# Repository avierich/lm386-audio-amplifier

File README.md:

# lM386 Audio Amplifier
This project is a simple 2 channel audio amp built around 2 LM386 1 Watt audio amplifiers.

The input to this amplifier is from a 2 channel computer audio output. The output is to 2 small speakers. The amplifier can be driven from a single supply ranging from +5V to +15V.

The final product was functional however slightly quiet. The LM386 amplifier IC's are best used as headphone amplifiers. I chose to use them since a very simple and small circuit could be desgined with them.

In the future I intend to create a new more powerful amplifier using discrete transistors instead.

The datasheet for the LM386 audio amplifier can be found [here](http://www.ti.com/lit/ds/symlink/lm386.pdf).

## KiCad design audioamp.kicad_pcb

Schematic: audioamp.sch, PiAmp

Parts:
Cb1, Cb2: 100u
Cd1, Cd2: 470u
Cdin1, Cdin2: 330n
Cf1, Cf2: 4.7u
Cg1, Cg2: 330n
Cs1: 100u
Pgin1: CONNECTOR
Pgndc1: CONNECTOR
Pgout1, Pgout2: CONNECTOR
Pin1, Pin2: CONNECTOR
Pout1, Pout2: CONNECTOR
Pvcc1: CONNECTOR
RF1, RF2: 10
RV1, RV2: 10k
Rg1, Rg2: 10k
U1, U2: LM386ALEX

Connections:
+12V: Cs1.1, Pvcc1.1, U1.6, U2.6
GND: Cb1.2, Cb2.2, Cs1.2, Pgin1.1, Pgndc1.1, Pgout1.1, Pgout2.1, RF1.2, RF2.2, RV1.3, RV2.3, U1.2, U1.4, U2.2, U2.4
unnamed: Cdin1.2, U1.3
unnamed: Cdin2.2, U2.3
unnamed: Cb2.1, U2.7
unnamed: Cf2.2, RF2.1
unnamed: Cb1.1, U1.7
unnamed: Pin1.1, RV1.1
unnamed: Cdin2.1, RV2.2
unnamed: Cdin1.1, RV1.2
unnamed: Pin2.1, RV2.1
unnamed: Cf1.2, RF1.1
unnamed: Cd1.2, Pout1.1
unnamed: Rg1.1, U1.1
unnamed: Cg1.2, Rg1.2
unnamed: Cg1.1, U1.8
unnamed: Cd2.2, Pout2.1
unnamed: Cg2.1, U2.8
unnamed: Cd2.1, Cf2.1, U2.5
unnamed: Cd1.1, Cf1.1, U1.5
unnamed: Rg2.1, U2.1
unnamed: Cg2.2, Rg2.2

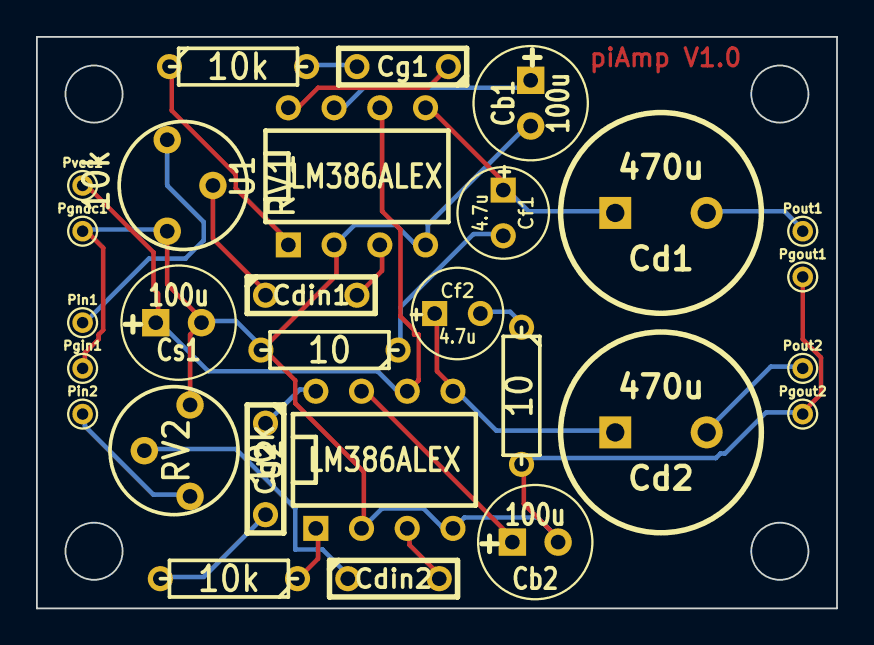
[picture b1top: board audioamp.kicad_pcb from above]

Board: 2 copper layers, 44.4 x 31.8 mm, 28 parts (0 on the bottom side), 22 nets.

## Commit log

2016-01-14 Adding files
